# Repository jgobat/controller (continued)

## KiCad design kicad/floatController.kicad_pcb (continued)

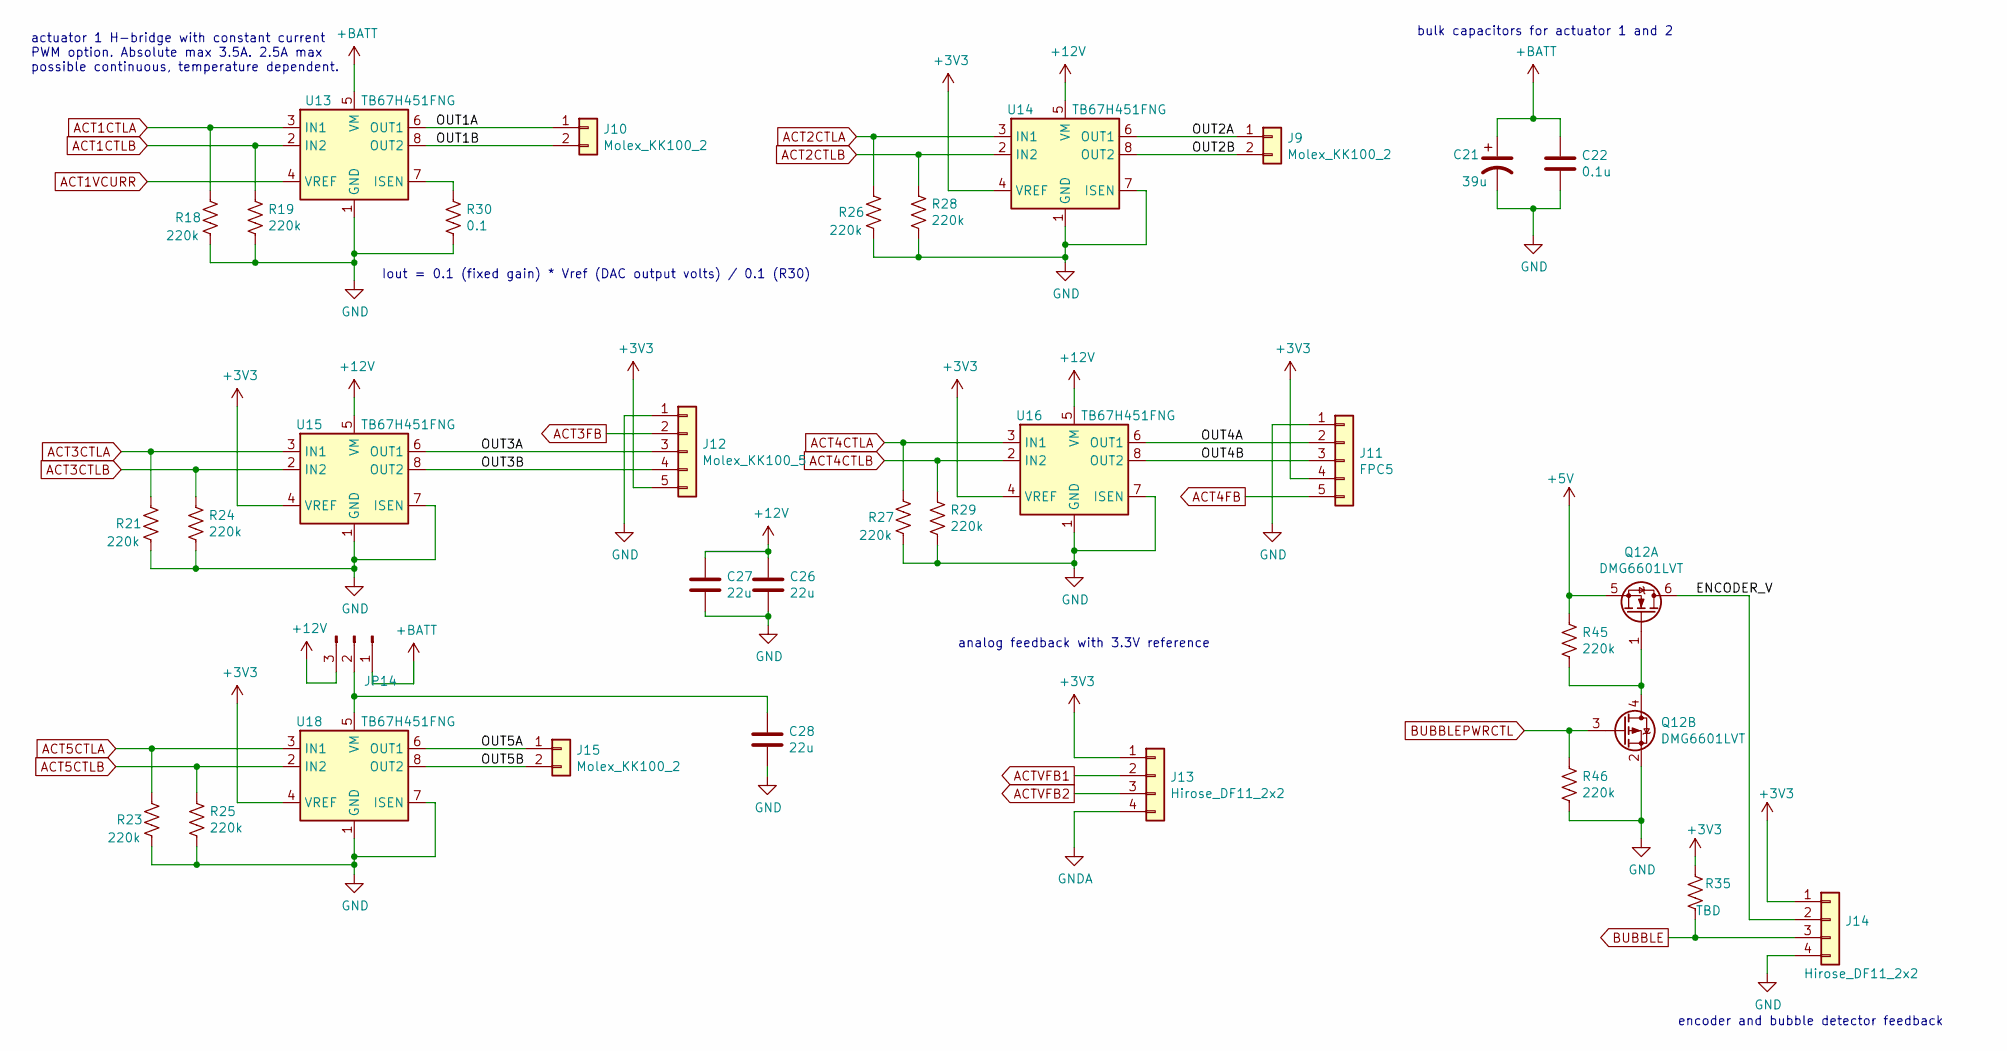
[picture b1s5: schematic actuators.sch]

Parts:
C21: 39u; CP_Elec_5x5.9; Manufacturer pn EEH-ZK1V390UR‎; Digikey P124997CT-ND
C22: 0.1u; C_0603_1608Metric_Pad1.05x0.95mm_HandSolder; Manufacturer pn GCJ188R71E104KA12D‎; Digikey 490-16477-1-ND
C26, C27, C28: 22u; C_1210_3225Metric_Pad1.42x2.65mm_HandSolder; Rating 25V
J9, J10, J15: Molex_KK100_2; Molex_KK-254_AE-6410-02A_1x02_P2.54mm_Vertical; Manufacturer pn 0022235021; Digikey WM13450-ND
J11: FPC5; Molex_200528-0050_1x05-1MP_P1.00mm_Horizontal
J12: Molex_KK100_5; Molex_KK-254_AE-6410-05A_1x05_P2.54mm_Vertical
J13, J14: Hirose_DF11_2x2; Hirose_DF11-4DP-2DSA_2x02_P2.00mm_Vertical; Manufacturer pn DF11-4DP-2DSA(08); Digikey H122036-ND
JP14: PinHead_2.54mm_3; PinHeader_1x03_P2.54mm_Vertical
Q12: DMG6601LVT; TSOT-23-6; Digikey ‎DMG6601LVT-7DICT-ND‎
R18, R19, R21, R23, R24, R25, R26, R27, R28, R29, R45, R46: 220k; R_0603_1608Metric_Pad1.05x0.95mm_HandSolder; Rating 5%, 1/10W; Manufacturer pn ERJ-3GEYJ224V; Digikey P220KGCT-ND
R30: 0.1; R_2512_6332Metric_Pad1.52x3.35mm_HandSolder; Rating 1%, 2W (4A); Manufacturer pn CSRN2512FTR100; Digikey CSRN2512FTR100CT-ND
R35: TBD; R_0603_1608Metric_Pad1.05x0.95mm_HandSolder
U13, U14, U15, U16, U18: TB67H451FNG; Texas_HTSOP-8-1EP_3.9x4.9mm_P1.27mm_EP2.95x4.9mm_Mask2.4x3.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; Rating 3A, pin compatible with DRV8870 with lo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; Manufacturer pn TB67H451FNG,EL; Digikey 264-TB67H451FNGELCT-ND

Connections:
+3V3: J11.4, J12.5, J13.1, J14.1, R35.1, U14.4 (VREF), U15.4 (VREF), U16.4 (VREF), U18.4 (VREF); also elsewhere on the board
+5V: Q12.5 (S), R45.1; also elsewhere on the board
+12V: C26.1, C27.1, JP14.3, U14.5 (VM), U15.5 (VM), U16.5 (VM); also elsewhere on the board
+BATT: C21.1, C22.1, JP14.1, U13.5 (VM); also elsewhere on the board
/actuators/ENCODER_V: J14.2, Q12.6 (D)
/actuators/OUT1A: J10.1, U13.6 (OUT1)
/actuators/OUT1B: J10.2, U13.8 (OUT2)
/actuators/OUT2A: J9.1, U14.6 (OUT1)
/actuators/OUT2B: J9.2, U14.8 (OUT2)
/actuators/OUT3A: J12.3, U15.6 (OUT1)
/actuators/OUT3B: J12.4, U15.8 (OUT2)
/actuators/OUT4A: J11.2, U16.6 (OUT1)
/actuators/OUT4B: J11.3, U16.8 (OUT2)
/actuators/OUT5A: J15.1, U18.6 (OUT1)
/actuators/OUT5B: J15.2, U18.8 (OUT2)
ACT1CTLA: R18.1, U13.3 (IN1); also elsewhere on the board
ACT1CTLB: R19.1, U13.2 (IN2); also elsewhere on the board
ACT1VCURR: U13.4 (VREF); also elsewhere on the board
ACT2CTLA: R26.1, U14.3 (IN1); also elsewhere on the board
ACT2CTLB: R28.1, U14.2 (IN2); also elsewhere on the board
ACT3CTLA: R21.1, U15.3 (IN1); also elsewhere on the board
ACT3CTLB: R24.1, U15.2 (IN2); also elsewhere on the board
ACT3FB: J12.2; also elsewhere on the board
ACT4CTLA: R27.1, U16.3 (IN1); also elsewhere on the board
ACT4CTLB: R29.1, U16.2 (IN2); also elsewhere on the board
ACT4FB: J11.5; also elsewhere on the board
ACT5CTLA: R23.1, U18.3 (IN1); also elsewhere on the board
ACT5CTLB: R25.1, U18.2 (IN2); also elsewhere on the board
ACTVFB1: J13.2; also elsewhere on the board
ACTVFB2: J13.3; also elsewhere on the board
BUBBLE: J14.3, R35.2; also elsewhere on the board
BUBBLEPWRCTL: Q12.3 (G), R46.1; also elsewhere on the board
GND: C21.2, C22.2, C26.2, C27.2, C28.2, J11.1, J12.1, J14.4, Q12.2 (S), R18.2, R19.2, R21.2, R23.2, R24.2, R25.2, R26.2, R27.2, R28.2, R29.2, R30.2, R46.2, U13.1 (GND), U13.9 (GND), U14.1 (GND), U14.7 (ISEN), U14.9 (GND), U15.1 (GND), U15.7 (ISEN), U15.9 (GND), U16.1 (GND), U16.7 (ISEN), U16.9 (GND), U18.1 (GND), U18.7 (ISEN), U18.9 (GND); also elsewhere on the board
GNDA: J13.4; also elsewhere on the board
unnamed: C28.1, JP14.2, U18.5 (VM)
unnamed: Q12.1 (G), Q12.4 (D), R45.2
unnamed: R30.1, U13.7 (ISEN)

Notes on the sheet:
analog feedback with 3.3V reference
encoder and bubble detector feedback
actuator 1 H-bridge with constant current PWM option. Absolute max 3.5A. 2.5A max possible continuous, temperature dependent.
bulk capacitors for actuator 1 and 2
Iout = 0.1 (fixed gain) * Vref (DAC output volts) / 0.1 (R30)

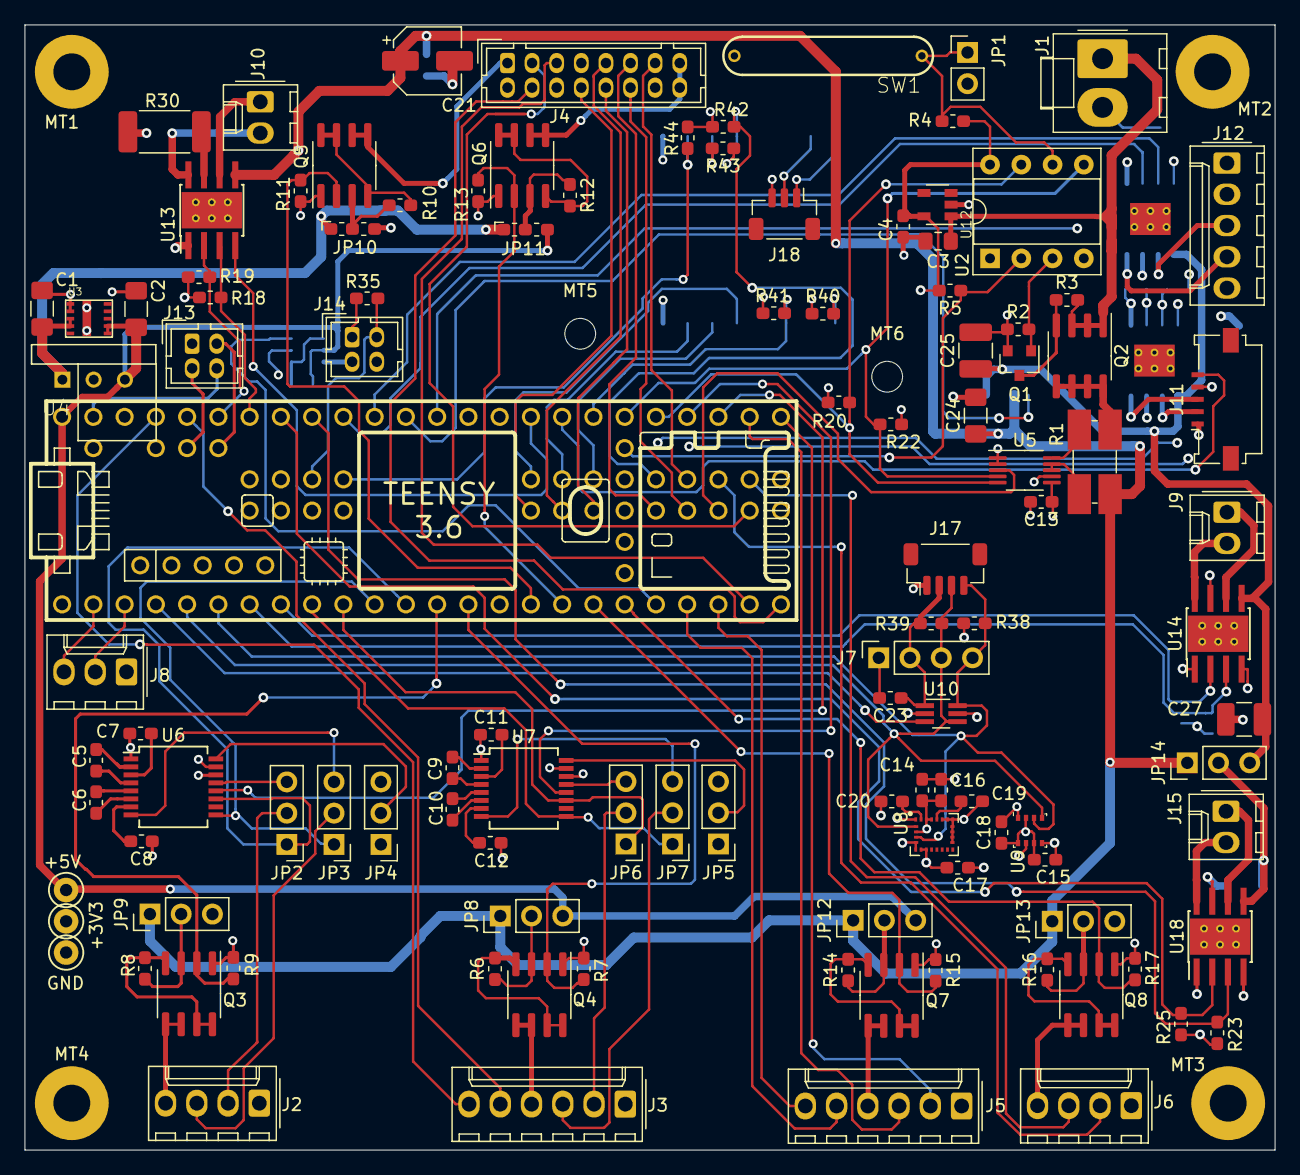
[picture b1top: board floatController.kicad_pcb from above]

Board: 4 copper layers, 101.6 x 91.4 mm, 136 parts (0 on the bottom side), 136 nets.

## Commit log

2021-12-19 sync up
